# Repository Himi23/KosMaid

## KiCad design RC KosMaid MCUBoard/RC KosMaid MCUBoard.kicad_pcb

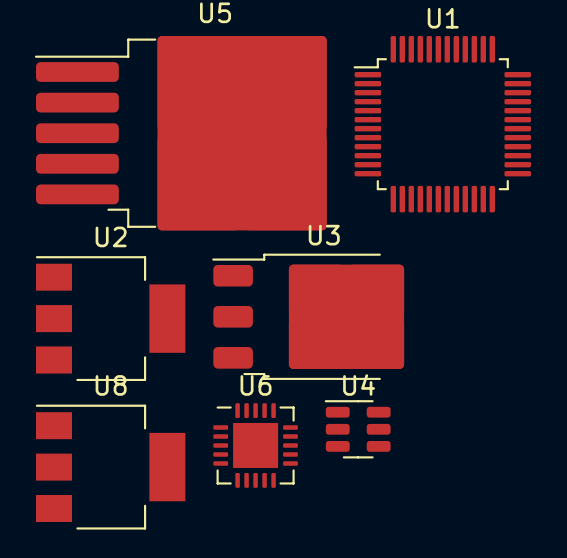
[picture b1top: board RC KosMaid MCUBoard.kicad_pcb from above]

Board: 2 copper layers, 7 parts (0 on the bottom side), 10 nets, no tracks yet.

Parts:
U1: STM32F103C8Tx; LQFP-48_7x7mm_P0.5mm
U2, U8: LM1117MP-3.3; SOT-223-3_TabPin2
U3: LM1117DT-5.0; TO-252-3_TabPin2
U4: USBLC6-2SC6; SOT-23-6
U5: XL4015; TO-263-5_TabPin3
U6: nRF24L01P; QFN-20-1EP_4x4mm_P0.5mm_EP2.5x2.5mm

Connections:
+3.3V: U1.24 (VDD), U1.36 (VDD), U1.48 (VDD), U8.2 (VO)
+3.3VA: U2.2 (VO), U6.7 (VDD), U6.15 (VDD), U6.18 (VDD)
+9V: U2.3 (VI), U3.3 (VI), U8.3 (VI)
GND: U1.8 (VSSA), U1.23 (VSS), U1.35 (VSS), U1.47 (VSS), U2.1 (GND), U5.1 (GND), U6.8 (VSS), U6.14 (VSS), U6.17 (VSS), U6.20 (VSS), U8.1 (GND)
PA2: U1.12 (PA2), U6.6 (IRQ)
PA3: U1.13 (PA3), U6.1 (CE)
PA4: U1.14 (PA4), U6.2 (CSN)
PA5: U1.15 (PA5), U6.3 (SCK)
PA6: U1.16 (PA6), U6.5 (MISO)
PA7: U1.17 (PA7), U6.4 (MOSI)
